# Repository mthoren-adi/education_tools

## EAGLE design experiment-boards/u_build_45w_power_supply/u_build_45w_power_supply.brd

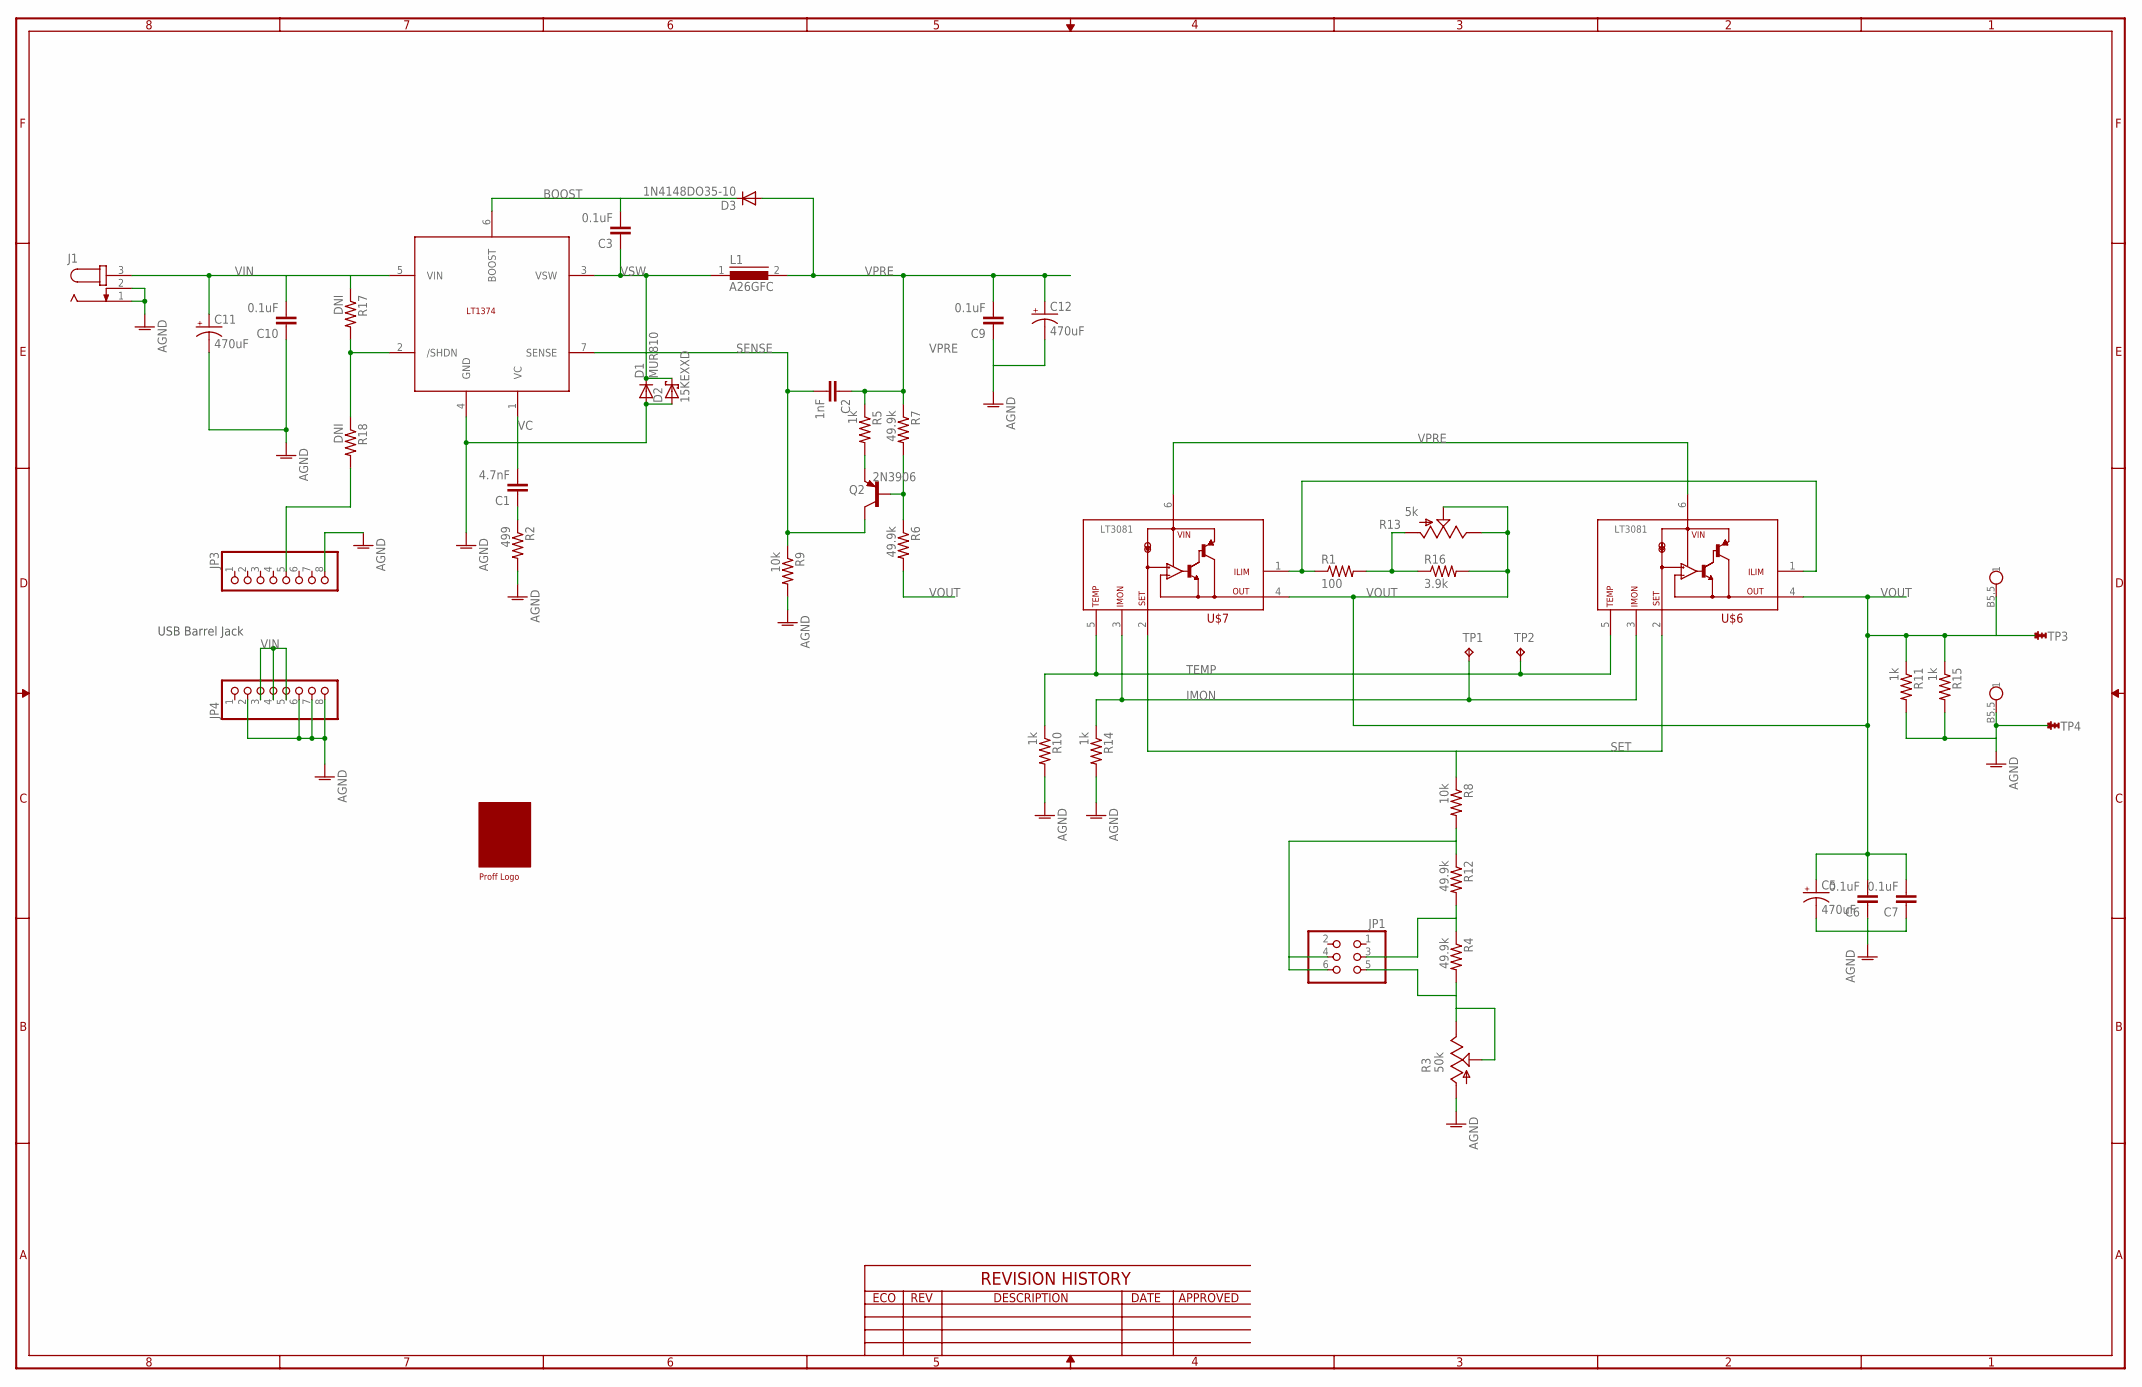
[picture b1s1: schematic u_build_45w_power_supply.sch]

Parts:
C1: 4.7nF; C050-025X075
C2: 1nF; C050-025X075
C3: 0.1uF; C050-025X075
C5, C11, C12: 470uF; E5-10,5
C6, C7, C9, C10: 0.1uF; C050-045X075
D1: MUR810; TO220ACS
D2: 15KEXXD; DO201T15
D3: 1N4148DO35-10; DO35-10
IC2: LT1374TO220-7; LT3081
J1: JACK-PLUG0; SPC4077
J5, J6: BAN_JACK1; PC_BAN_JACK
JP1: PINHD-2X3; 2X03
JP3, JP4: PINHD-1X8; 1X08
L1: A26GFC
Q2: 2N3906; TO92
R1: 100; 0207/10
R2: 499; 0207/10
R3: 50k; RS3
R4, R6, R7, R12: 49.9k; 0207/10
R5, R10, R11, R14, R15: 1k; 0207/10
R8, R9: 10k; 0207/10
R13: 5k; RS3
R16: 3.9k; 0207/10
R17, R18: DNI; 0207/10
TP1, TP2: TPPAD1-13; P1-13
TP3, TP4: TURRET0.092; TURRET_MILLMAX_2501-2
U$1: PROFF
U$6, U$7: LT3081

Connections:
AGND: C5.-, C6.1, C7.1, C9.1, C10.1, C11.-, C12.-, D1.A, D2.A, IC2.4 (GND), J1.1, J1.2, J6.B5,5, JP3.8, JP4.2, JP4.6, JP4.7, JP4.8, R2.2, R3.A, R9.2, R10.2, R11.2, R14.2, R15.2, TP4.1
BOOST: C3.2, D3.C, IC2.6 (BOOST)
ILIM: R1.1, U$6.1 (ILIM), U$7.1 (ILIM)
IMON: R14.1, TP1.TP, U$6.3 (IMON), U$7.3 (IMON)
unnamed: C1.1, R2.1
unnamed: IC2.2 (/SHDN), R17.2, R18.1
unnamed: JP1.5, R3.E, R3.S, R4.2
unnamed: JP1.3, R4.1, R12.2
unnamed: R1.2, R13.A, R16.1
unnamed: JP3.5, R18.2
unnamed: JP1.4, JP1.6, R8.2, R12.1
unnamed: Q2.2 (B), R6.1, R7.2
unnamed: Q2.3 (E), R5.2
SENSE: C2.2, IC2.7 (SENSE), Q2.1 (C), R9.1
SET: R8.1, U$6.2 (SET), U$7.2 (SET)
TEMP: R10.1, TP2.TP, U$6.5 (TEMP), U$7.5 (TEMP)
VC: C1.2, IC2.1 (VC)
VIN: C10.2, C11.+, IC2.5 (VIN), J1.3, JP4.3, JP4.4, JP4.5, R17.1
VOUT: C5.+, C6.2, C7.2, J5.B5,5, R6.2, R11.1, R13.E, R13.S, R15.1, R16.2, TP3.1, U$6.4 (OUT), U$7.4 (OUT)
VPRE: C2.1, C9.2, C12.+, D3.A, L1.2, R5.1, R7.1, U$6.6 (VIN), U$7.6 (VIN)
VSW: C3.1, D1.C, D2.C, IC2.3 (VSW), L1.1

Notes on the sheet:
USB Barrel Jack

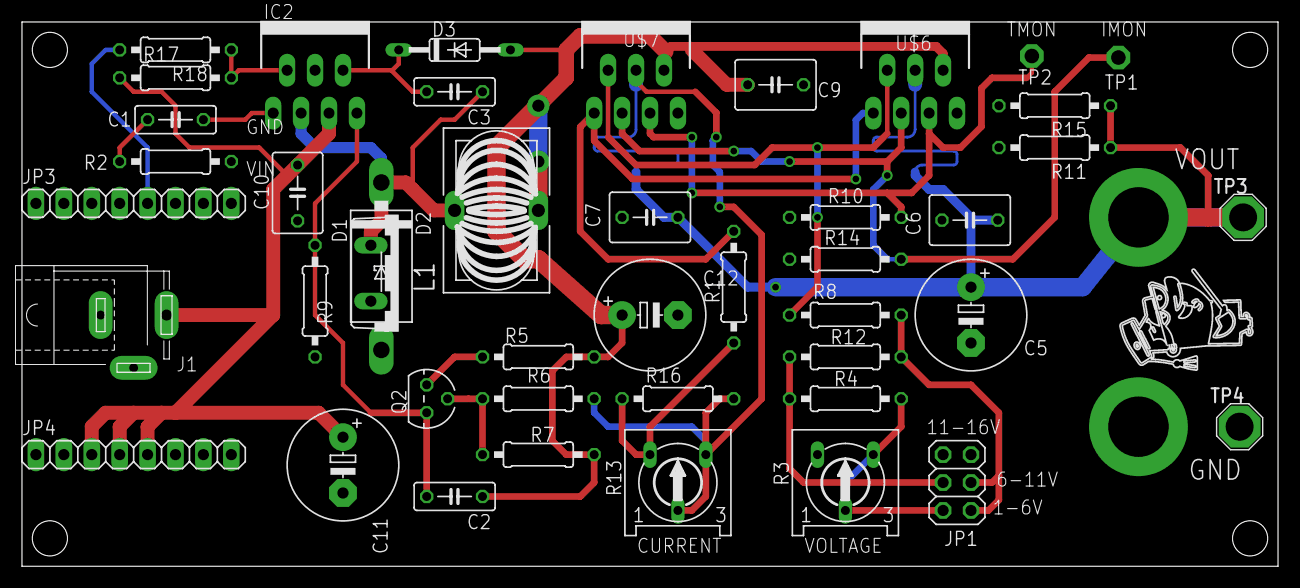
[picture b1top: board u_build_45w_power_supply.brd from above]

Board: 2 copper layers, 114.3 x 49.5 mm, 47 parts (0 on the bottom side), 21 nets.

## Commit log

2018-12-07 Initial commit for efficiency lab.
2018-12-07 Add comments
2018-12-09 Move ammeter to the correct location.
2021-05-04 Adding wein bridge oscillator circuit
2023-08-05 Add You Build It 45W Power Supply LTspice and Eagle files.
2023-10-14 Initial release
    This is the inital release of the first 5 m1k accessory PC boards.
2023-10-14 Add single amplifier buffer board
    Intial release of the single amplifier input buffer board.
    Initial release of the transistor op-amp experimant board
2023-10-14 Add Eagle files for SIP version of discrete op-amp
2023-10-14 add more boards
    Design files etc. added for LTC1043 based analog mux board and adjustable pot voltagedivider board
2023-10-14 Adding more board files
    Adding cad files for lumped LC trnasmission line board.
2023-10-14 modify header spacing
    Moved the analog mux input header on to 0.1" grid centers
2023-10-14 Adding more board files
    Adding more accessory board files to the inventory
2023-10-14 Add some M2k boards
    Add CAD files for 2 M2k analog Mux boards and CAD files for M2k Breadboard adapter
2023-10-21 Put accessory boards in directories. Add LTspice. Add gerbers. Add 45W power supply.
2024-02-09 Adding flip-flop experiment simulations
